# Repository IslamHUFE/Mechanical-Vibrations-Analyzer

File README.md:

# Mechanical Vibrations Analyzer

A compact **mechanical vibration monitoring system** designed to be mounted directly on a machine and visualize its vibration behavior as a **real-time spectrogram**.

The device is designed around a custom PCB, a mechanical enclosure, and an embedded vibration-sensing system. After mounting the unit to a machine using screws, the machine can be operated while its vibration characteristics are displayed on the onboard screen as a frequency-versus-time spectrogram.

> **Project status:** Hardware design completed.

## Project Overview

The main idea of the project is to provide a self-contained vibration-monitoring device that can be physically attached to machinery and used to observe its vibration spectrum.

### Basic workflow

1. Mount the analyzer to the machine using the enclosure mounting points.
2. Operate the machine under the desired condition.
3. Capture mechanical vibrations using the onboard vibration sensor.
4. Process the measured vibration data.
5. Display the resulting frequency content as a spectrogram on the device's screen.

This makes it possible to visually observe how the machine's vibration spectrum changes over time.

## Hardware Design

The hardware was designed as a custom PCB specifically for the vibration-monitoring application. The repository contains the KiCad design files together with the supporting 3D/CAD files used during the mechanical design process.

### PCB 3D Views

The following renders show the assembled PCB from different viewing angles.

<table>
<tr>
<td align="center" width="33%">
<br>
<b>PCB 3D View — Front Perspective</b><br>
<sub>Three-dimensional view of the completed PCB from a front perspective.</sub>
</td>
<td align="center" width="33%">
<br>
<b>PCB 3D View — Rear Perspective</b><br>
<sub>Three-dimensional view showing the opposite side of the assembled board.</sub>
</td>
<td align="center" width="33%">
<br>
<b>PCB 3D View — Overall Assembly</b><br>
<sub>Additional 3D perspective highlighting the board layout and component placement.</sub>
</td>
</tr>
</table>

## PCB Layer Stackup

The next renders show the complete PCB layer arrangement followed by the individual layers in order.

<table>
<tr>
<td align="center" width="33%">
<br>
<b>Complete PCB Layer Stack</b><br>
<sub>All six PCB layers shown together to illustrate the complete board layout.</sub>
</td>
<td align="center" width="33%">
<br>
<b>Layer 1</b><br>
<sub>First individual PCB layer in the layer sequence.</sub>
</td>
<td align="center" width="33%">
<br>
<b>Layer 2</b><br>
<sub>Second individual PCB layer in the layer sequence.</sub>
</td>
</tr>
<tr>
<td align="center" width="33%">
<br>
<b>Layer 3</b><br>
<sub>Third individual PCB layer in the layer sequence.</sub>
</td>
<td align="center" width="33%">
<br>
<b>Layer 4</b><br>
<sub>Fourth individual PCB layer in the layer sequence.</sub>
</td>
<td align="center" width="33%">
<br>
<b>Layer 5</b><br>
<sub>Fifth individual PCB layer in the layer sequence.</sub>
</td>
</tr>
<tr>
<td align="center" width="33%">
<br>
<b>Layer 6</b><br>
<sub>Sixth and final individual PCB layer in the layer sequence.</sub>
</td>
<td></td>
<td></td>
</tr>
</table>

## Mechanical Enclosure

A dedicated enclosure was designed for the PCB using **FreeCAD**. The enclosure provides a physical housing for the electronics and allows the analyzer to be securely mounted to the machine during measurements.

<table>
<tr>
<td align="center" width="50%">
<br>
<b>FreeCAD Enclosure — Design View</b><br>
<sub>CAD model of the custom enclosure designed around the PCB.</sub>
</td>
<td align="center" width="50%">
<br>
<b>FreeCAD Enclosure — Final View</b><br>
<sub>Additional enclosure view showing the mechanical housing and mounting geometry.</sub>
</td>
</tr>
</table>

## Design Files

The repository includes the main hardware-design files used to develop the analyzer, including:

- **KiCad schematic and PCB files** for the electronic design.
- **3D component models** used for PCB visualization.
- **FreeCAD/CAD-related files** for the mechanical enclosure.
- Supporting configuration and project files used during PCB development.

## Applications

The analyzer can be used as a compact tool for observing vibration behavior in rotating or mechanically moving equipment. A spectrogram provides a convenient way to see both the frequency content and how it evolves over time.

Potential uses include:

- Machine vibration monitoring
- Mechanical system diagnostics
- Observation of rotating machinery vibration
- Experimental vibration analysis
- Educational demonstrations of frequency-domain analysis

## Project Post

More details about the hardware development and the project progress are available in the project's LinkedIn post:

**[Mechanical Vibrations Analyzer — Hardware Development](https://www.linkedin.com/posts/islamhufe_%D8%AE%D9%84%D8%B5%D8%AA-%D8%A7%D9%85%D8%A8%D8%A7%D8%B1%D8%AD-%D8%AC%D8%B2%D8%A1-%D8%A7%D9%84%D9%87%D8%A7%D8%B1%D8%AF%D9%88%D9%8A%D8%B1-%D9%85%D9%86-%D9%85%D8%B4%D8%B1%D9%88%D8%B9-%D8%A8%D8%A7%D8%B3%D9%85-mechanical-activity-7492970094948519936-9O9D)**

## Author

**Islam Tarek Moawad**

Designed and developed as an embedded hardware project combining **PCB design, vibration sensing, signal analysis, embedded systems, and mechanical CAD**.

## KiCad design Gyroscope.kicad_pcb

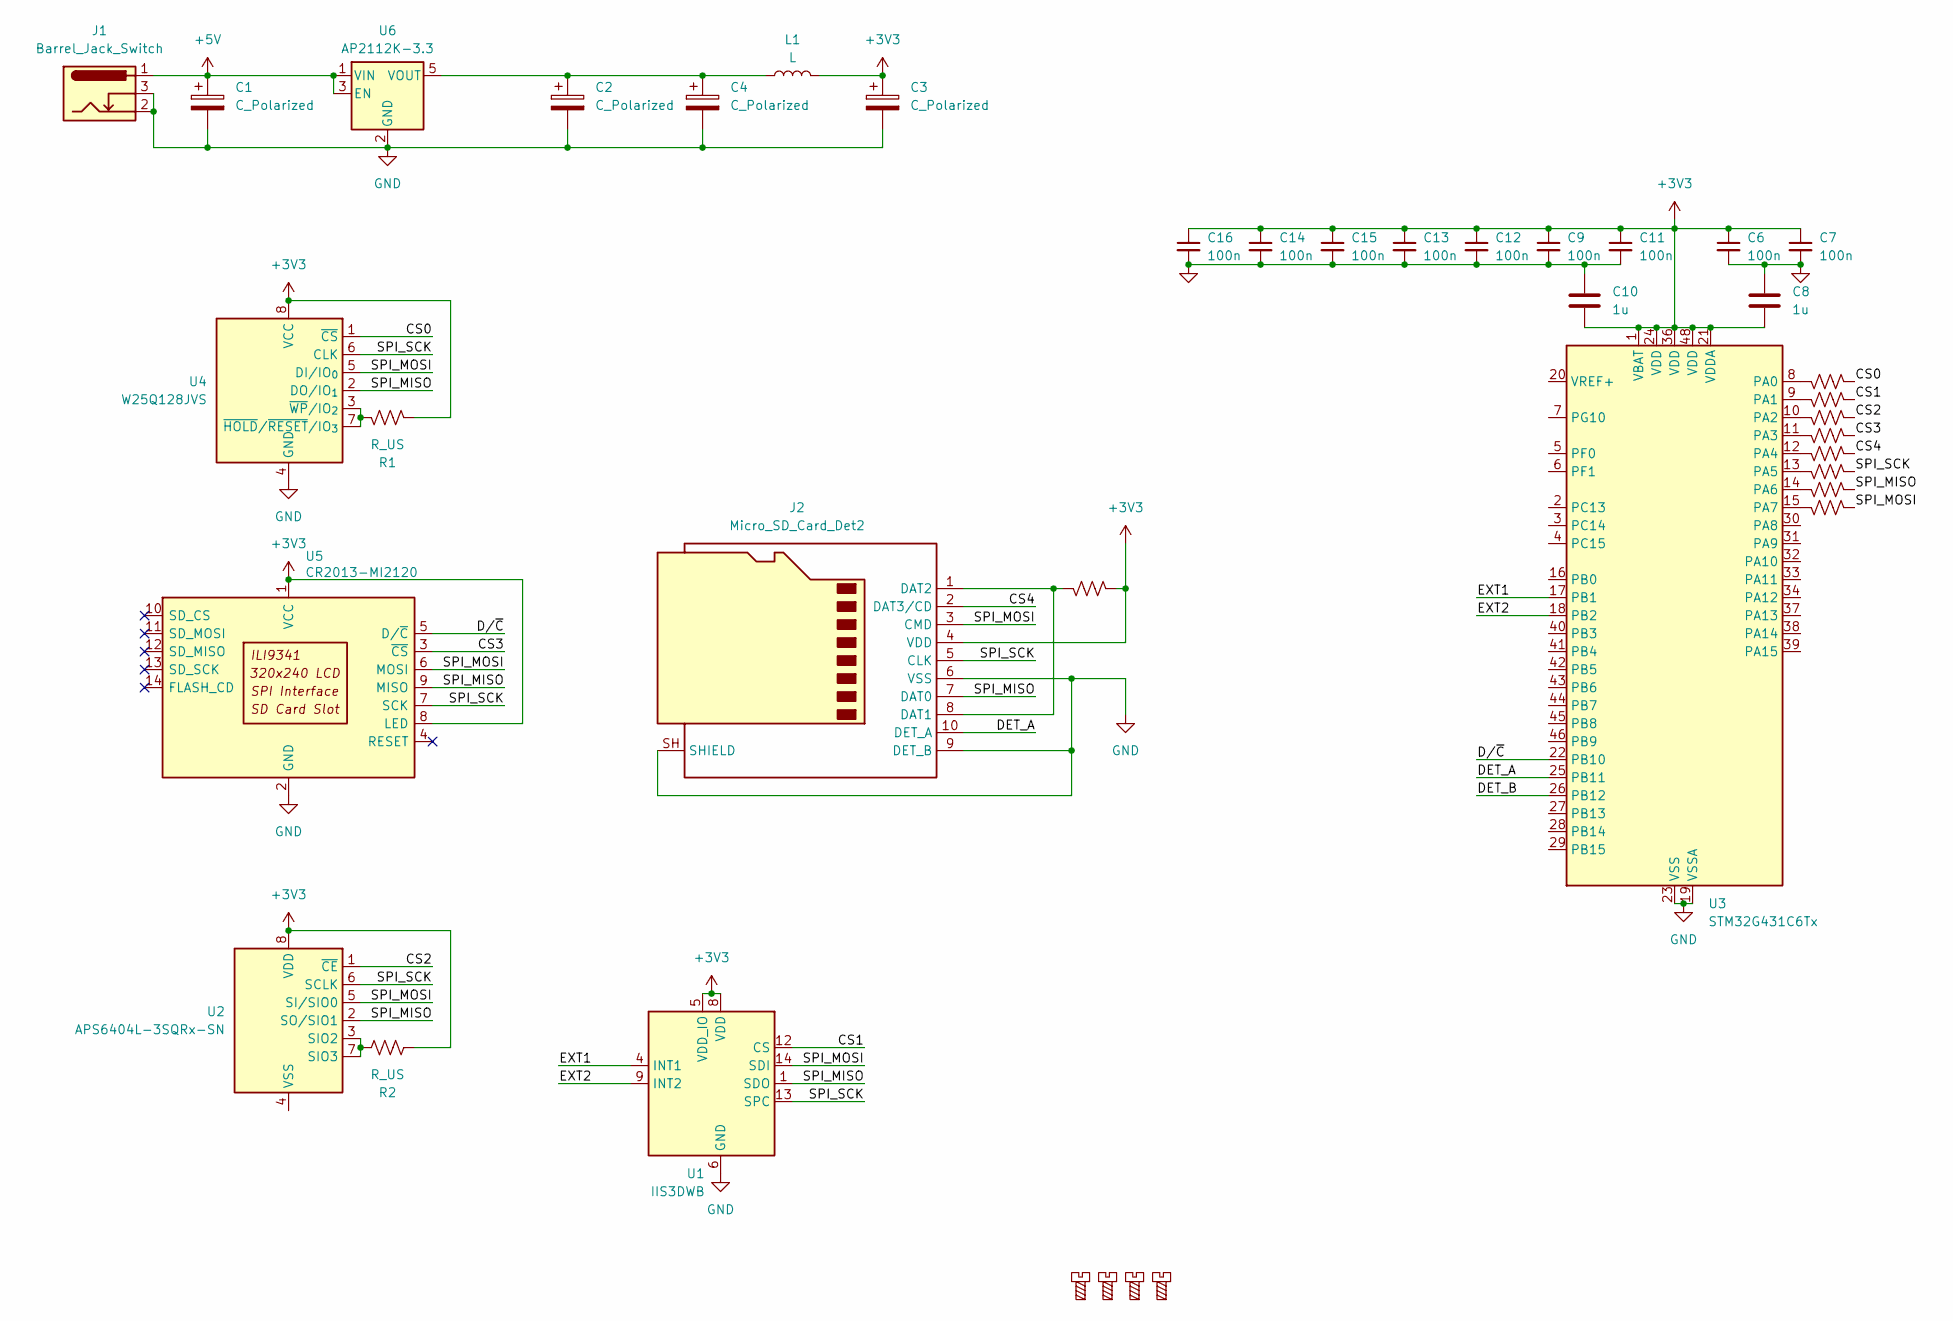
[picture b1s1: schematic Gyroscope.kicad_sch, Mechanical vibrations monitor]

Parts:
C1, C2, C3, C4: C_Polarized; CP_EIA-3528-12_Kemet-T
C6, C7, C9, C11, C12, C13, C14, C15, C16: 100n; C_0402_1005Metric
C8, C10: 1u; C_0805_2012Metric
H1, H2, H3, H4: MountingScrew; MountingHole_2.2mm_M2_DIN965_Pad_TopBottom
J1: Barrel_Jack_Switch; BarrelJack_GCT_DCJ200-10-A_Horizontal
J2: Micro_SD_Card_Det2; microSD_HC_Hirose_DM3AT-SF-PEJM5
L1: L; L_Neosid_SM-PIC0512H
R1, R2, R3, R4, R5, R6, R7, R8, R9, R10, R11: R_US; R_0402_1005Metric_Pad0.72x0.64mm_HandSolder
U1: IIS3DWB; LGA-14_3x2.5mm_P0.5mm_LayoutBorder3x4y; MPN IIS3DWBTR
U2: APS6404L-3SQRx-SN; SOIC-8_3.9x4.9mm_P1.27mm
U3: STM32G431C6Tx; LQFP-48_7x7mm_P0.5mm
U4: W25Q128JVS; SOIC-8_5.3x5.3mm_P1.27mm
U5: CR2013-MI2120
U6: AP2112K-3.3; SOT-23-5

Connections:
+3V3: C3.1, C6.1, C7.1, C8.2, C9.1, C10.2, C11.1, C12.1, C13.1, C14.1, C15.1, C16.1, J2.4 (VDD), L1.2, R1.1, R2.2, R3.1, U1.5 (VDD_IO), U1.8 (VDD), U2.8 (VDD), U3.1 (VBAT), U3.21 (VDDA), U3.24 (VDD), U3.36 (VDD), U3.48 (VDD), U4.8 (VCC), U5.1 (VCC), U5.8 (LED)
+5V: C1.1, J1.1, U6.1 (VIN), U6.3 (EN)
/CS0: R4.1, U4.1 (~CS)
/CS1: R5.1, U1.12 (CS)
/CS2: R6.1, U2.1 (~CE)
/CS3: R7.1, U5.3 (~CS)
/CS4: J2.2 (DAT3/CD), R8.1
/DET_A: J2.10 (DET_A), U3.25 (PB11)
/DET_B: U3.26 (PB12)
/D/~C: U3.22 (PB10), U5.5 (D/~C)
/EXT1: U1.4 (INT1), U3.17 (PB1)
/EXT2: U1.9 (INT2), U3.18 (PB2)
/SPI_MISO: J2.7 (DAT0), R10.1, U1.1 (SDO), U2.2 (SO/SIO1), U4.2 (DO/IO_{1}), U5.9 (MISO)
/SPI_MOSI: J2.3 (CMD), R11.1, U1.14 (SDI), U2.5 (SI/SIO0), U4.5 (DI/IO_{0}), U5.6 (MOSI)
/SPI_SCK: J2.5 (CLK), R9.1, U1.13 (SPC), U2.6 (SCLK), U4.6 (CLK), U5.7 (SCK)
GND: C1.2, C2.2, C3.2, C4.2, C6.2, C7.2, C8.1, C9.2, C10.1, C11.2, C12.2, C13.2, C14.2, C15.2, C16.2, J1.2, J1.3, J2.6 (VSS), J2.9 (DET_B), J2.SH (SHIELD), U1.2 (GND), U1.3 (GND), U1.6 (GND), U1.7 (GND), U3.19 (VSSA), U3.23 (VSS), U3.35 (VSS), U3.47 (VSS), U4.4 (GND), U5.2 (GND), U6.2 (GND)
unnamed: J2.1 (DAT2), J2.8 (DAT1), R3.2
unnamed: R2.1, U2.3 (SIO2), U2.7 (SIO3)
unnamed: R4.2, U3.8 (PA0)
unnamed: R5.2, U3.9 (PA1)
unnamed: R6.2, U3.10 (PA2)
unnamed: R7.2, U3.11 (PA3)
unnamed: R8.2, U3.12 (PA4)
unnamed: R9.2, U3.13 (PA5)
unnamed: R10.2, U3.14 (PA6)
unnamed: R11.2, U3.15 (PA7)
unnamed: R1.2, U4.3 (~WP/IO_{2}), U4.7 (~HOLD/~RESET/IO_{3})
unnamed: C2.1, C4.1, L1.1, U6.5 (VOUT)

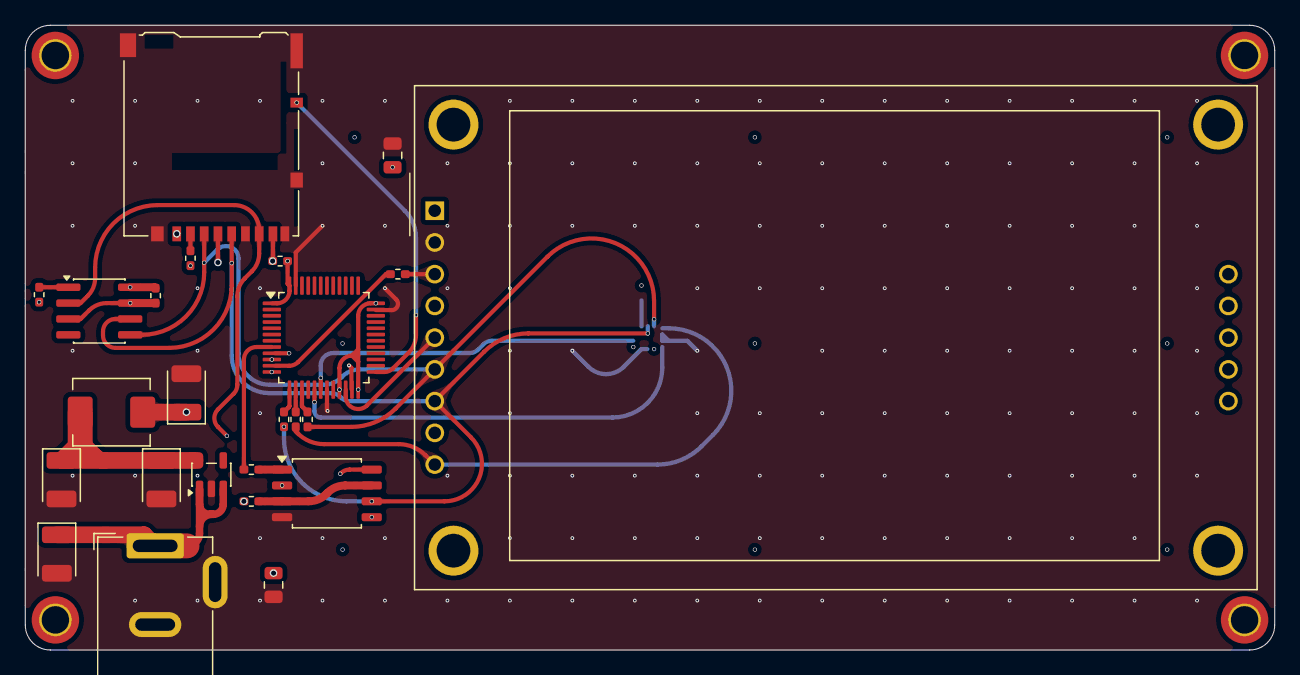
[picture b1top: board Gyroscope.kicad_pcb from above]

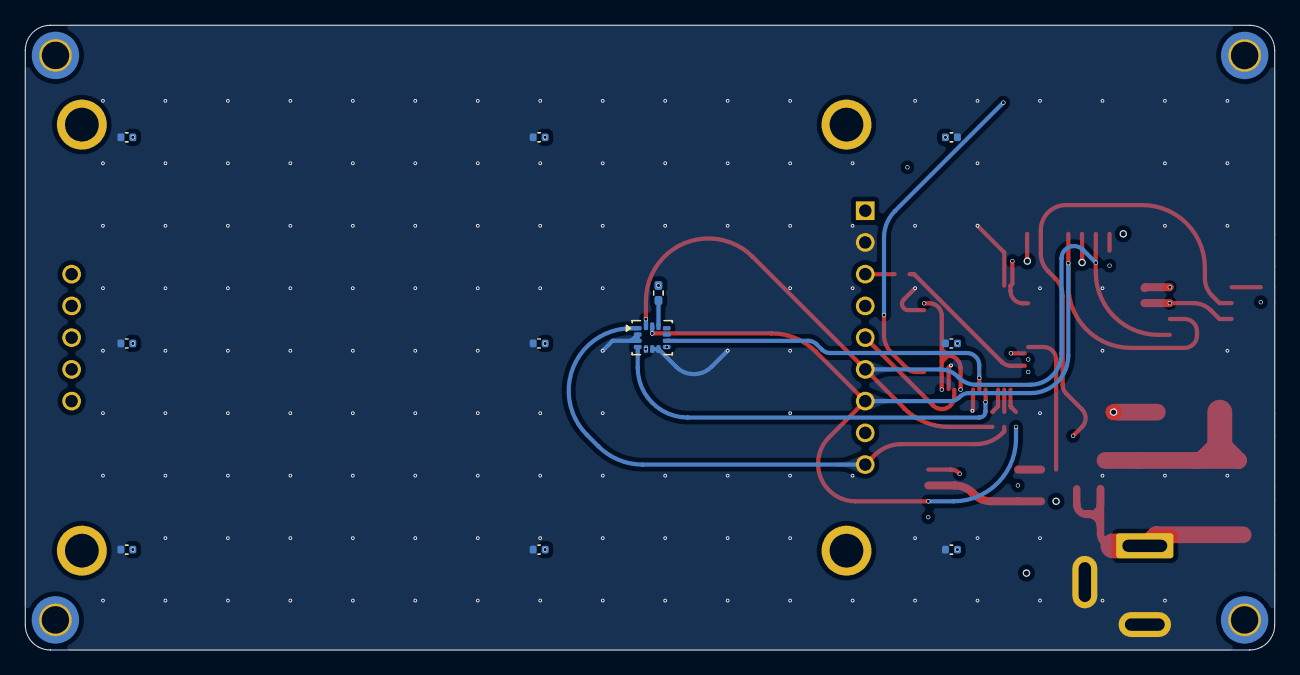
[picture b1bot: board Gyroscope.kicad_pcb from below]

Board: 6 copper layers, 100.0 x 50.0 mm, 39 parts (11 on the bottom side), 27 nets.

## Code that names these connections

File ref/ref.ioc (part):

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Mcu.Name=STM32G431C(6-8-B)Tx
Mcu.Package=LQFP48
Mcu.UserName=STM32G431C6Tx
PA0.Signal=GPIO_Output
PA1.Signal=GPIO_Output
PA14.Signal=GPXTI14
PA15.Signal=GPXTI15
PA2.Signal=GPIO_Output
PA3.Signal=GPIO_Output
PA4.Signal=GPIO_Output
PA5.Mode=Full_Duplex_Master
PA5.Signal=SPI1_SCK
PA6.Mode=Full_Duplex_Master
PA6.Signal=SPI1_MISO
PA7.Mode=Full_Duplex_Master
PA7.Signal=SPI1_MOSI
PB0.Signal=GPIO_Output
PB1.Signal=GPXTI1
PB10.Signal=GPIO_Output
PB11.Signal=GPIO_Output
PB12.Signal=GPIO_Output
PB2.Signal=GPXTI2
RCC.HSE_VALUE=8000000
RCC.SYSCLKFreq_VALUE=170000000
RCC.SYSCLKSource=RCC_SYSCLKSOURCE_PLLCLK
board=custom
